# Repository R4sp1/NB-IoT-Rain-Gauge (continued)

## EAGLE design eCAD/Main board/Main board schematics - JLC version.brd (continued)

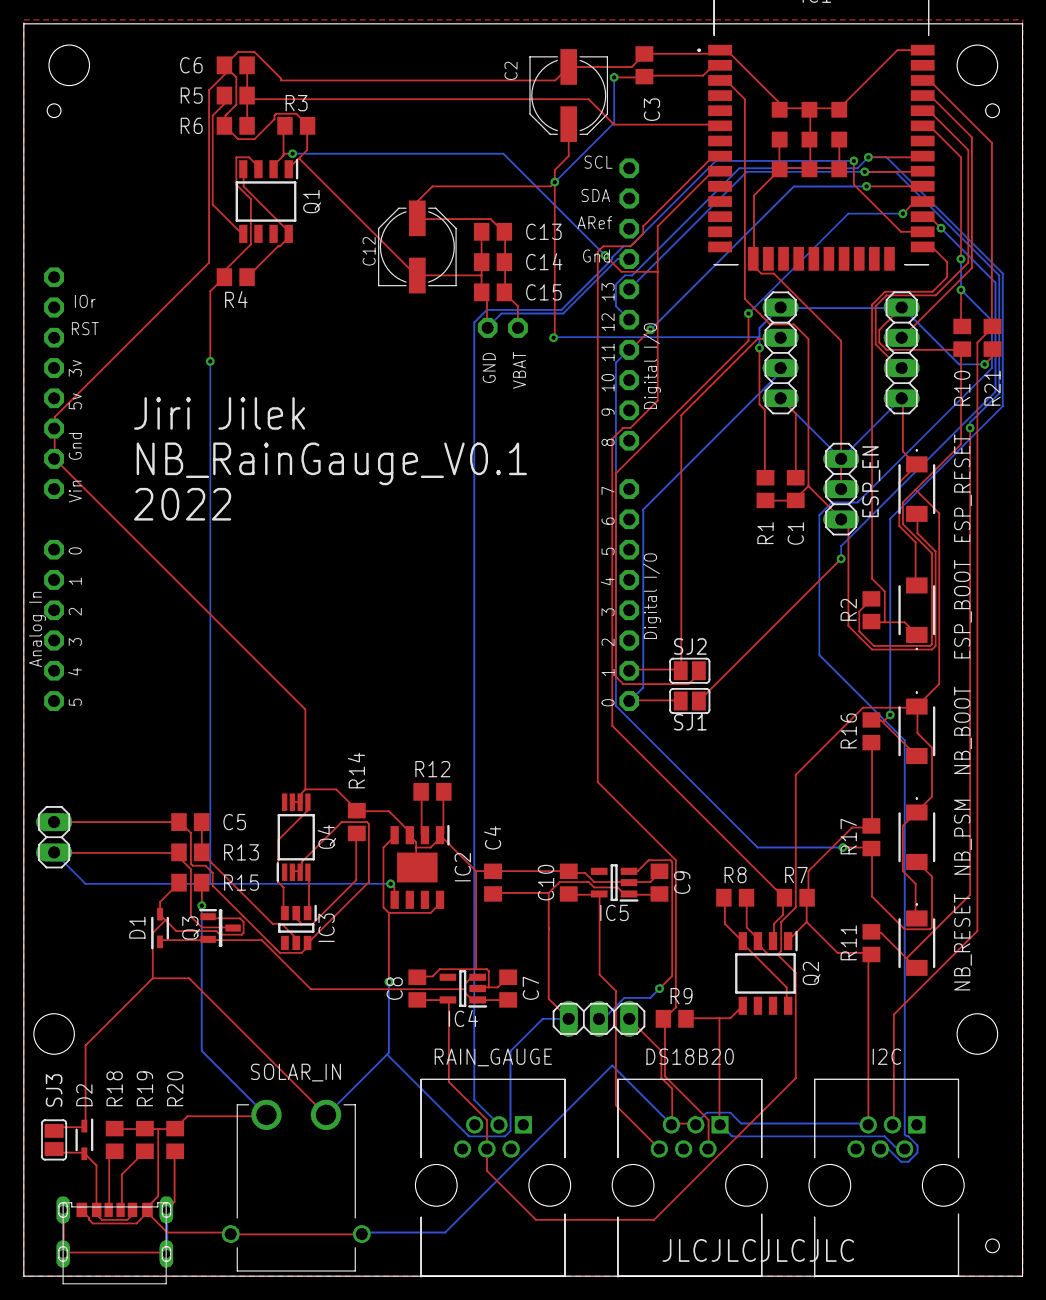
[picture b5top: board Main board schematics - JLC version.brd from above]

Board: 2 copper layers, 83.8 x 105.1 mm, 65 parts (0 on the bottom side), 38 nets.

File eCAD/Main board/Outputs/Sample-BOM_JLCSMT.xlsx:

Comment | Designator | Footprint | JLCPCB Part #（optional）
 | BAT_IN | 1X02
 | ESP_EN, FAN | 1X03
 | SJ1, SJ2, SJ3 | SJ
100R | R13 | R0805
100n | C3, C5, C6, C13 | C0805
100p | C15 | C0805
10K | R1, R2, R11, R16, R17 | R0805
10k | R3, R4, R5, R6, R7, R8, R10, R15, R21 | R0805
10u | C4 | C0805
1M | R20 | R0805
1N4148WS-7-F | D1, D2 | SOD2513X120N | C191023
1k | R14 | R0805
1u | C1, C7, C8, C9, C10 | C0805
220u | C2, C12 | PANASONIC_D
22p | C14 | C0805
4k7 | R9 | R0805
5k1 | R18, R19 | R0805
ARDUINOR3-BPLACE | U1 | ARDUINOR3
DW01A-G | IC3 | SOT95P280X135-6N | C61503
ESP32-WROOM-32E_M113EH3200PH3Q | IC1 | ESP32WROOM32EM113EH3200PH3Q0 | C701341
FS8205A | Q4 | SOP65P640X120-8N | C16052
IRF7319TRPBF | Q1, Q2 | SOIC127P600X175-8N
ME6211C33M5G-N | IC4, IC5 | SOT95P270X145-5N | C82942
RJE01-660-01 | DS18B20, I2C, RAIN_GAUGE | RJE0166001
Rprog | R12 | R0805
SI2347DS-T1-GE3 | Q3 | SOT95P237X112-3N
TP4056X | IC2 | SOIC127P600X175-9N | C16581
TS-1088-AR02016 | ESP_BOOT, ESP_RESET, NB_BOOT, NB_PSM, NB_RESET | TS1088AR02016 | C720477
UART_FLASH | JP1 | 1X04
UART_NB | JP4 | 1X04
USBC-6P | U$1 | USCX-06FX-XXMX-01
XT30PW-M | SOLAR_IN | XT30PWM

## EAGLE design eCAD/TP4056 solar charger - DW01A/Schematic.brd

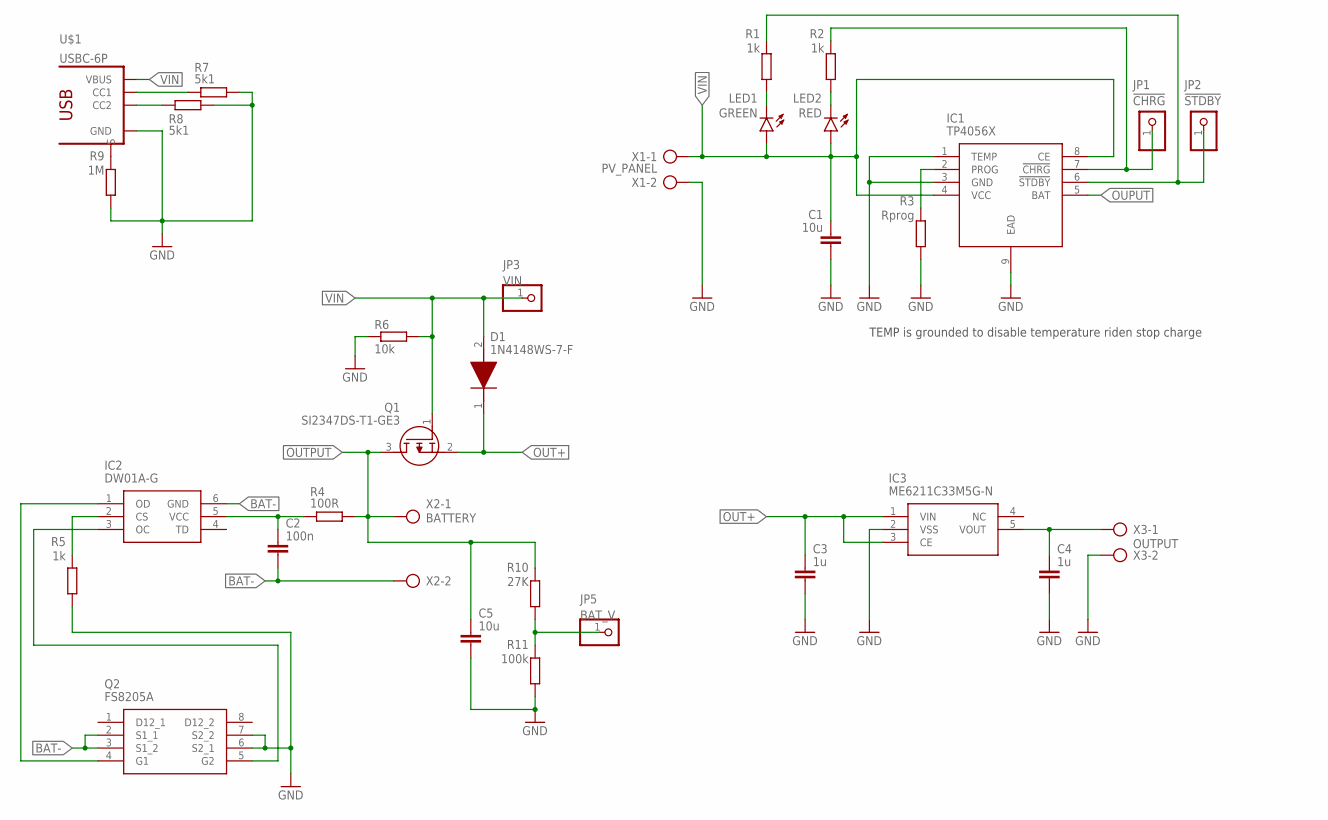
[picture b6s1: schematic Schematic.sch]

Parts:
C1, C5: 10u; C0805
C2: 100n; C0805
C3, C4: 1u; C0805
D1: 1N4148WS-7-F; SOD2513X120N
IC1: TP4056X; SOIC127P600X175-9N
IC2: DW01A-G; SOT95P280X135-6N
IC3: ME6211C33M5G-N; SOT95P270X145-5N
JP1: !CHRG; 1X01
JP2: !STDBY; 1X01
JP3: VIN; 1X01
JP5: BAT_V; 1X01
LED1: GREEN; CHIPLED_0805
LED2: RED; CHIPLED_0805
Q1: SI2347DS-T1-GE3; SOT95P237X112-3N
Q2: FS8205A; SOP65P640X120-8N
R1, R2, R5: 1k; R0805
R3: Rprog; R0805
R4: 100R; R0805
R6: 10k; R0805
R7, R8: 5k1; R0805
R9: 1M; R0805
R10: 27K; R0805
R11: 100k; R0805
U$1: USBC-6P; USCX-06FX-XXMX-01
X1: PV_PANEL; AK300/2
X2: BATTERY; AK300/2
X3: OUTPUT; AK300/2

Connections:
BAT-: C2.2, IC2.6 (GND), Q2.2 (S1_1), Q2.3 (S1_2), X2.2
GND: C1.2, C3.2, C4.2, C5.2, IC1.1 (TEMP), IC1.3 (GND), IC1.9 (EAD), IC3.2 (VSS), Q2.6 (S2_1), Q2.7 (S2_2), R3.2, R5.1, R6.1, R7.1, R8.1, R9.2, R11.1, U$1.GND1 (GND), U$1.GND2 (GND), X1.2, X3.2
unnamed: LED1.C, R1.2
unnamed: LED2.C, R2.2
unnamed: IC1.6 (!STDBY), JP2.1, R1.1
unnamed: IC1.2 (PROG), R3.1
unnamed: C2.1, IC2.5 (VCC), R4.1
unnamed: IC1.7 (!CHRG), JP1.1, R2.1
unnamed: R9.1, U$1.SHIELD1 (S), U$1.SHIELD2 (S), U$1.SHIELD3 (S), U$1.SHIELD4 (S)
unnamed: R8.2, U$1.CC2
unnamed: IC2.2 (CS), R5.2
unnamed: IC2.1 (OD), Q2.4 (G1)
unnamed: R7.2, U$1.CC1
unnamed: IC2.3 (OC), Q2.5 (G2)
unnamed: C4.1, IC3.5 (VOUT), X3.1
unnamed: JP5.1, R10.1, R11.2
OUPUT: IC1.5 (BAT)
OUT+: C3.1, D1.1 (K), IC3.1 (VIN), IC3.3 (CE), Q1.2 (S)
OUTPUT: C5.1, Q1.3 (D), R4.2, R10.2, X2.1
VIN: C1.1, D1.2 (A), IC1.4 (VCC), IC1.8 (CE), JP3.1, LED1.A, LED2.A, Q1.1 (G), R6.2, U$1.VBUS1 (VBUS), U$1.VBUS2 (VBUS), X1.1

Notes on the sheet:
TEMP is grounded to disable temperature riden stop charge

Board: 2 copper layers, 32 parts (0 on the bottom side), 19 nets, no tracks yet.

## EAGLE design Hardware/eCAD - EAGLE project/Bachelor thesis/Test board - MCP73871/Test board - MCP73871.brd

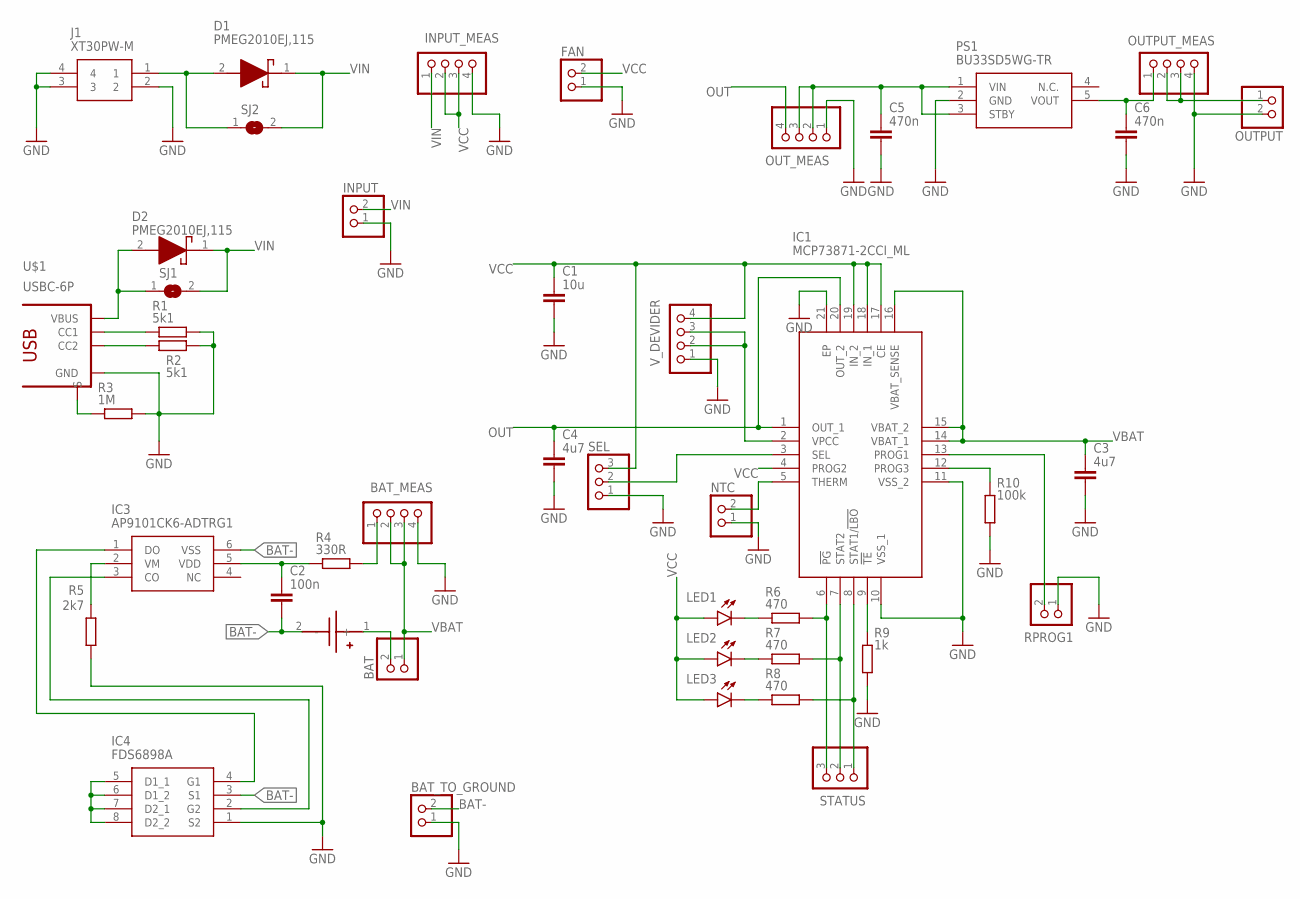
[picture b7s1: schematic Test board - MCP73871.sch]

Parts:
BAT: PINHD-1X2; 1X02
BAT_MEAS: PINHD-1X4; 1X04
BAT_TO_GROUND: PINHD-1X2; 1X02
C1: 10u; C0805
C2: 100n; C0805
C3, C4: 4u7; C0805
C5, C6: 470n; C0805
D1, D2: PMEG2010EJ,115; SODFL2512X80N
FAN: PINHD-1X2; 1X02
IC1: MCP73871-2CCI_ML; QFN50P400X400X100-21N
IC3: AP9101CK6-ADTRG1; SOT95P285X140-6N
IC4: FDS6898A; SOIC127P600X175-8N
INPUT: PINHD-1X2; 1X02
INPUT_MEAS: PINHD-1X4; 1X04
J1: XT30PW-M; XT30PWM
LED1: !PG; CHIPLED_0805
LED2: STAT2; CHIPLED_0805
LED3: STAT1; CHIPLED_0805
NTC: PINHD-1X2; 1X02
OUTPUT: PINHD-1X2; 1X02
OUTPUT_MEAS: PINHD-1X4; 1X04
OUT_MEAS: PINHD-1X4; 1X04
PS1: BU33SD5WG-TR; SOT95P280X125-5N
R1, R2: 5k1; R0805
R3: 1M; R0805
R4: 330R; R0805
R5: 2k7; R0805
R6, R7, R8: 470; R0805
R9: 1k; R0805
R10: 100k; R0805
RPROG1: PINHD-1X2; 1X02
SEL: PINHD-1X3; 1X03
SJ1, SJ2: SJ
STATUS: PINHD-1X3; 1X03
U$1: USBC-6P; USCX-06FX-XXMX-01
U$2: BLOSSOM-BLM-18650-1PCS
V_DEVIDER: PINHD-1X4; 1X04

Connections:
!PG: IC1.6 (!PG), R6.2, STATUS.3
!TE: IC1.9 (!TE), R9.1
BAT+: BAT.2, U$2.1 (+)
BAT-: BAT_TO_GROUND.2, C2.2, IC3.6 (VSS), IC4.3 (S1), U$2.2 (-)
CC1: R1.1, U$1.CC1
CC2: R2.1, U$1.CC2
DRAIN: IC4.5 (D1_1), IC4.6 (D1_2), IC4.7 (D2_1), IC4.8 (D2_2)
G1: IC3.1 (DO), IC4.4 (G1)
G2: IC3.3 (CO), IC4.2 (G2)
GND: BAT_MEAS.4, BAT_TO_GROUND.1, C1.2, C3.2, C4.2, C5.2, C6.2, FAN.1, IC1.10 (VSS_1), IC1.11 (VSS_2), IC1.21 (EP), IC4.1 (S2), INPUT.1, INPUT_MEAS.4, J1.2, J1.3, J1.4, NTC.1, OUTPUT.2, OUTPUT_MEAS.4, OUT_MEAS.1, PS1.2 (GND), R1.2, R2.2, R3.2, R5.1, R9.2, R10.2, RPROG1.1, SEL.1, U$1.GND1 (GND), U$1.GND2 (GND), V_DEVIDER.1
LDO_VIN: C5.1, OUT_MEAS.2, OUT_MEAS.3, PS1.1 (VIN), PS1.3 (STBY)
unnamed: C2.1, IC3.5 (VDD), R4.1
unnamed: LED1.C, R6.1
unnamed: LED2.C, R7.1
unnamed: LED3.C, R8.1
unnamed: BAT_MEAS.1, R4.2
OUT: C4.1, IC1.1 (OUT_1), IC1.20 (OUT_2), OUT_MEAS.4
OUTPUT: OUTPUT.1, OUTPUT_MEAS.2, OUTPUT_MEAS.3
PROG1: IC1.13 (PROG1), RPROG1.2
PROG3: IC1.12 (PROG3), R10.1
PV_IN: D1.2 (A), J1.1, SJ2.1
S: R3.1, U$1.SHIELD1 (S), U$1.SHIELD2 (S), U$1.SHIELD3 (S), U$1.SHIELD4 (S)
SEL: IC1.3 (SEL), SEL.2
STAT1: IC1.8 (STAT1/!LBO), R8.2, STATUS.1
STAT2: IC1.7 (STAT2), R7.2, STATUS.2
THERM: IC1.5 (THERM), NTC.2
VBAT: BAT.1, BAT_MEAS.2, BAT_MEAS.3, C3.1, IC1.14 (VBAT_1), IC1.15 (VBAT_2), IC1.16 (VBAT_SENSE)
VBUS: D2.2 (A), SJ1.1, U$1.VBUS1 (VBUS), U$1.VBUS2 (VBUS)
VCC: C1.1, FAN.2, IC1.4 (PROG2), IC1.17 (CE), IC1.18 (IN_1), IC1.19 (IN_2), INPUT_MEAS.2, INPUT_MEAS.3, LED1.A, LED2.A, LED3.A, SEL.3, V_DEVIDER.4
VIN: D1.1 (K), D2.1 (K), INPUT.2, INPUT_MEAS.1, SJ1.2, SJ2.2
VM: IC3.2 (VM), R5.2
VOUT: C6.1, OUTPUT_MEAS.1, PS1.5 (VOUT)
VPCC: IC1.2 (VPCC), V_DEVIDER.2, V_DEVIDER.3

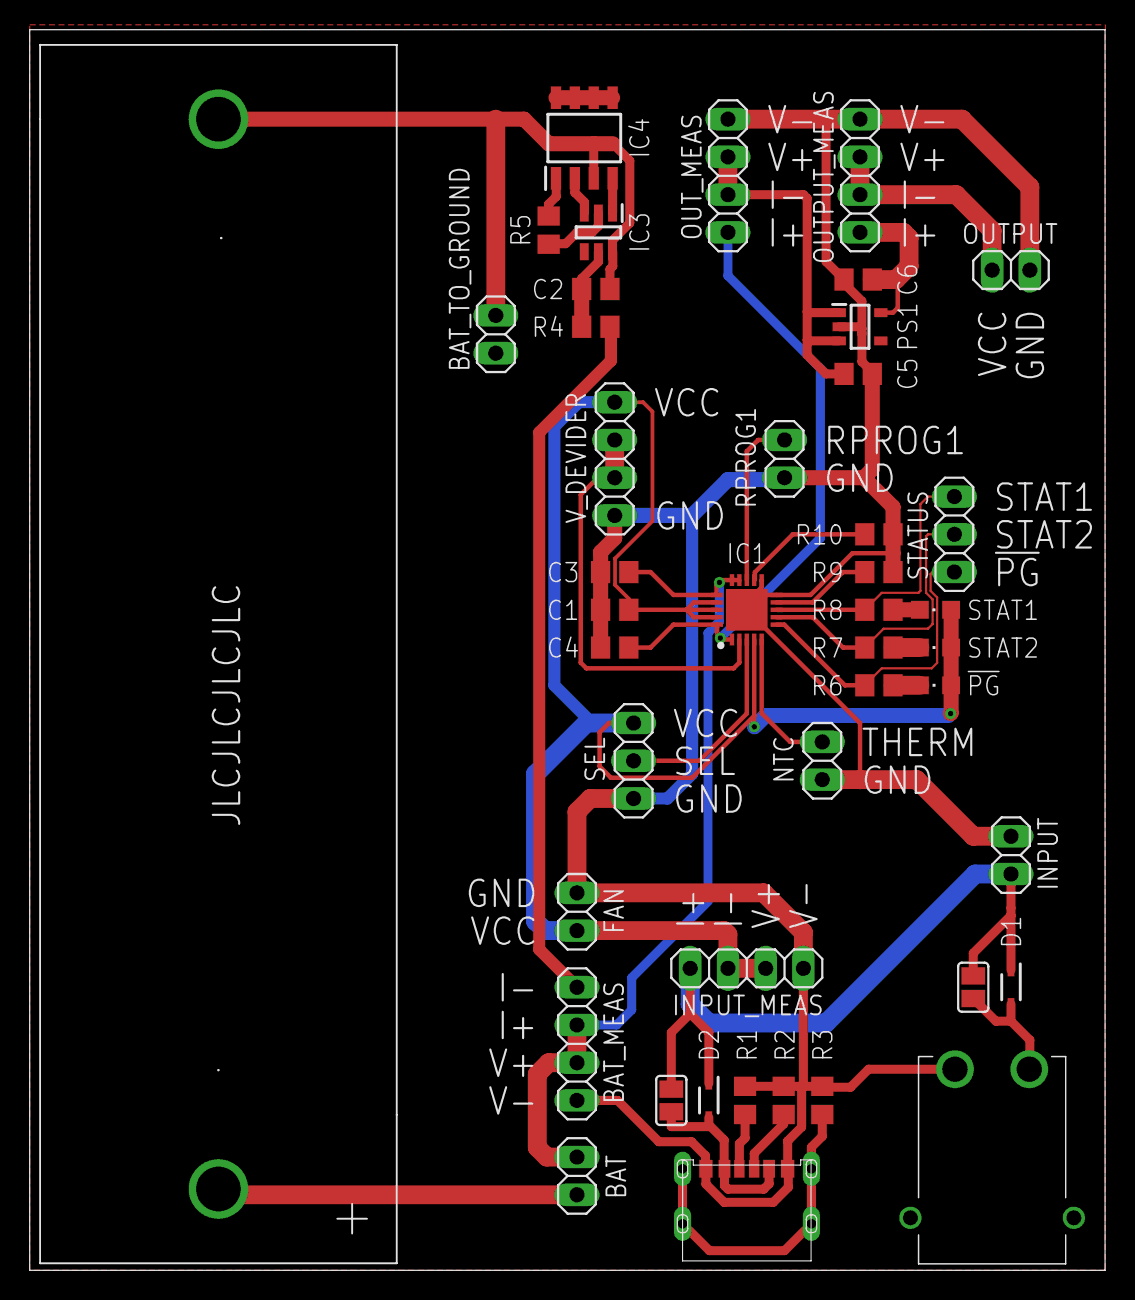
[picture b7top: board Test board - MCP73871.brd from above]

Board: 2 copper layers, 72.4 x 83.5 mm, 44 parts (0 on the bottom side), 33 nets.

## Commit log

2022-10-08 Added BUT .tex template
2022-10-15 Added code to test deep sleep on ESP32
2022-10-15 Added lines to ignore VS code stuff
2022-10-15 Schematics of solar charger based on TP4056
2022-10-16 Changed packeges to 0805
2022-10-16 gitignored Eagle files
2022-10-16 Deleted ignored files
2022-10-16 Deleted ignored file
2022-10-16 Compile test
2022-10-16 VS code gitignore
2022-10-18 Schematic export to pdf and png
2022-10-20 Temp sensors test code
2022-10-23 Board design
2022-10-23 Added second bme280 sensor to test
2022-10-26 RTC example and test
2022-10-27 Added second DS18B and light sensor, removed ESP32 internal temp sensor as it isn't precise on low temps
2022-10-27 Made holes biggeer to be able to manufacture it
2022-10-28 DW01A schematic, removed eagle.epf from gitignore
2022-10-28 Main board schematics
2022-10-30 Added uart programming interface
2022-11-05 Battery managment board test code
2022-11-10 Change sleep time to 1 min
2022-11-10 Created version of charger with JLC stock parts
2022-11-13 Hardware serial to com with Quectel devkit
2022-11-13 Using ESP32 internal RTC synced via NTP
2022-11-13 Added power circuits, connection to Quectel devkit
2022-11-27 Board for semestral project done
2022-11-27 Tests
2022-12-05 Made test work on breadboard
2022-12-08 Test on V0.1 board
2022-12-09 Hardware test with I2C light sensor, temp, rain and battery measurment
2022-12-11 Added second temp sensor
2022-12-11 Repair mistakes: C2, flash pin on ESP, fan pinout
2022-12-11 Pushed to Fusion
2022-12-11 Uncommneted code
2022-12-11 Renamed file and added references to used libs
2022-12-11 Added README in Czech lang - info from IS VUT
2022-12-13 Text of the work added
2023-01-23 Added CSV data of tests
2023-02-01 Added Eagle project for future designs, now including wire connection and VEML7700 brakeout boards design
2023-02-02 Separated wire connection board and VEM7700 brakeout board, to VEML7700 board added R and C acording to datasheet
2023-02-02 Added WiFi support
2023-02-05 Imported main board to project
2023-02-18 Function to round number to two decimal places added
2023-02-20 Final touches
2023-02-20 Defined out technologies which will not be used
2023-02-26 pin definition correction
2023-02-26 UDP testing code
2023-02-26 Project changes
2023-02-26 Production files
2023-02-26 Production data
2023-02-26 I2C pull-up Rs added on switched source
2023-02-26 Work around Quectel BC660K NB-IoT module
2023-03-04 Quic test program for data collection
2023-03-04 .dru file added
2023-03-04 Work around Quectel BC660K-GL module
2023-03-10 Test with UDP send via NB-IoT
2023-03-18 Completed antena interface, power circuitry
2023-03-21 Main board .brd added
2023-03-22 component placement
2023-03-24 Routing
2023-03-31 v2 board out in production
2023-03-31 Deleted wifi func
2023-03-31 deleted no longer needed files
2023-04-09 Removed not longer needed code
2023-04-09 Added test sketch for VEML7700 lux sensor
2023-04-09 Debounce test code
2023-05-02 Misc
2023-05-02 Debounce, VEML7700, init variables
    *Debounced callback for rain gauge input
    *Added code support for VEML7700 light sensor - replaced BH1750 sensor code
    *init variables to default states (helps parse data on backend)
2023-05-12 Changed default values for temp and light to -127. Used RA flag for UDP send.
2023-05-12 Added DEVICE_ADDRESS to identify devices on server
2023-05-12 Formatting and typos
2023-05-12 Added checkConnection()
2023-05-18 deleted unnecessary files
2023-05-18 Corrected mistakes
2023-05-18 Upload to second board
2023-05-18 cleanup
2023-05-23 Reorder of files, added 3D models and NodeRED flow
2023-05-23 Removed unused libraries, added coments
2023-05-24 Added sample credentials file
2023-06-14 Moved voltage devider calibration to server
2023-06-14 Update build path
2023-06-14 build output
2023-06-14 build path
2023-06-14 remove build output
2023-06-21 Added WiFi version
2023-09-25 Added READMEs
2023-11-21 RJ12 connectors wireup description
2023-11-21 Firmware with new added sensors (SHT45, BME280)
